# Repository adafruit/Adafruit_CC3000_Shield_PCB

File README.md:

# Adafruit CC3000 Shield PCB
&nbsp; <br />
Click to view in the Adafruit Shop:
- [Adafruit CC3000 WiFi Shield with uFL Connector for Ext Antenna (DISCONTINUED)](https://www.adafruit.com/product/1534)
- [Adafruit HUZZAH CC3000 WiFi Shield with Onboard Antenna (DISCONTINUED)](https://www.adafruit.com/product/1491)

The CC3000 hits that sweet spot of usability, price and capability. It uses SPI for communication (not UART!) so you can push data as fast as you want or as slow as you want. It has a proper interrupt system with IRQ pin so you can have asynchronous connections. It supports 802.11b/g, open/WEP/WPA/WPA2 security, TKIP & AES. A built in TCP/IP stack with a "BSD socket" interface. TCP and UDP in both client and server mode, up to 4 concurrent sockets. It does not support "AP" mode, it can connect to an access point but it cannot be an access point.

**Please note that the CC3000 module is discontinued and we suggest the [Adafruit Airlift products](https://www.adafruit.com/?q=airlift) as a replacement** - it has SSL support, soft-AP capability, and is more reliable.

PCB files for Adafruit CC3000 Shields. The format is EagleCAD schematic and board layout

For more details, check out the product page at

-----> http://www.adafruit.com/products/1534
-----> http://www.adafruit.com/products/1491

### License

Adafruit invests time and resources providing this open source design, please support Adafruit and open-source hardware by [purchasing products from Adafruit](https://www.adafruit.com)!

All text above must be included in any redistribution

Designed by Limor Fried/Ladyada for Adafruit Industries.
Creative Commons Attribution/Share-Alike, all text above must be included in any redistribution. 
See license.txt for additional information.

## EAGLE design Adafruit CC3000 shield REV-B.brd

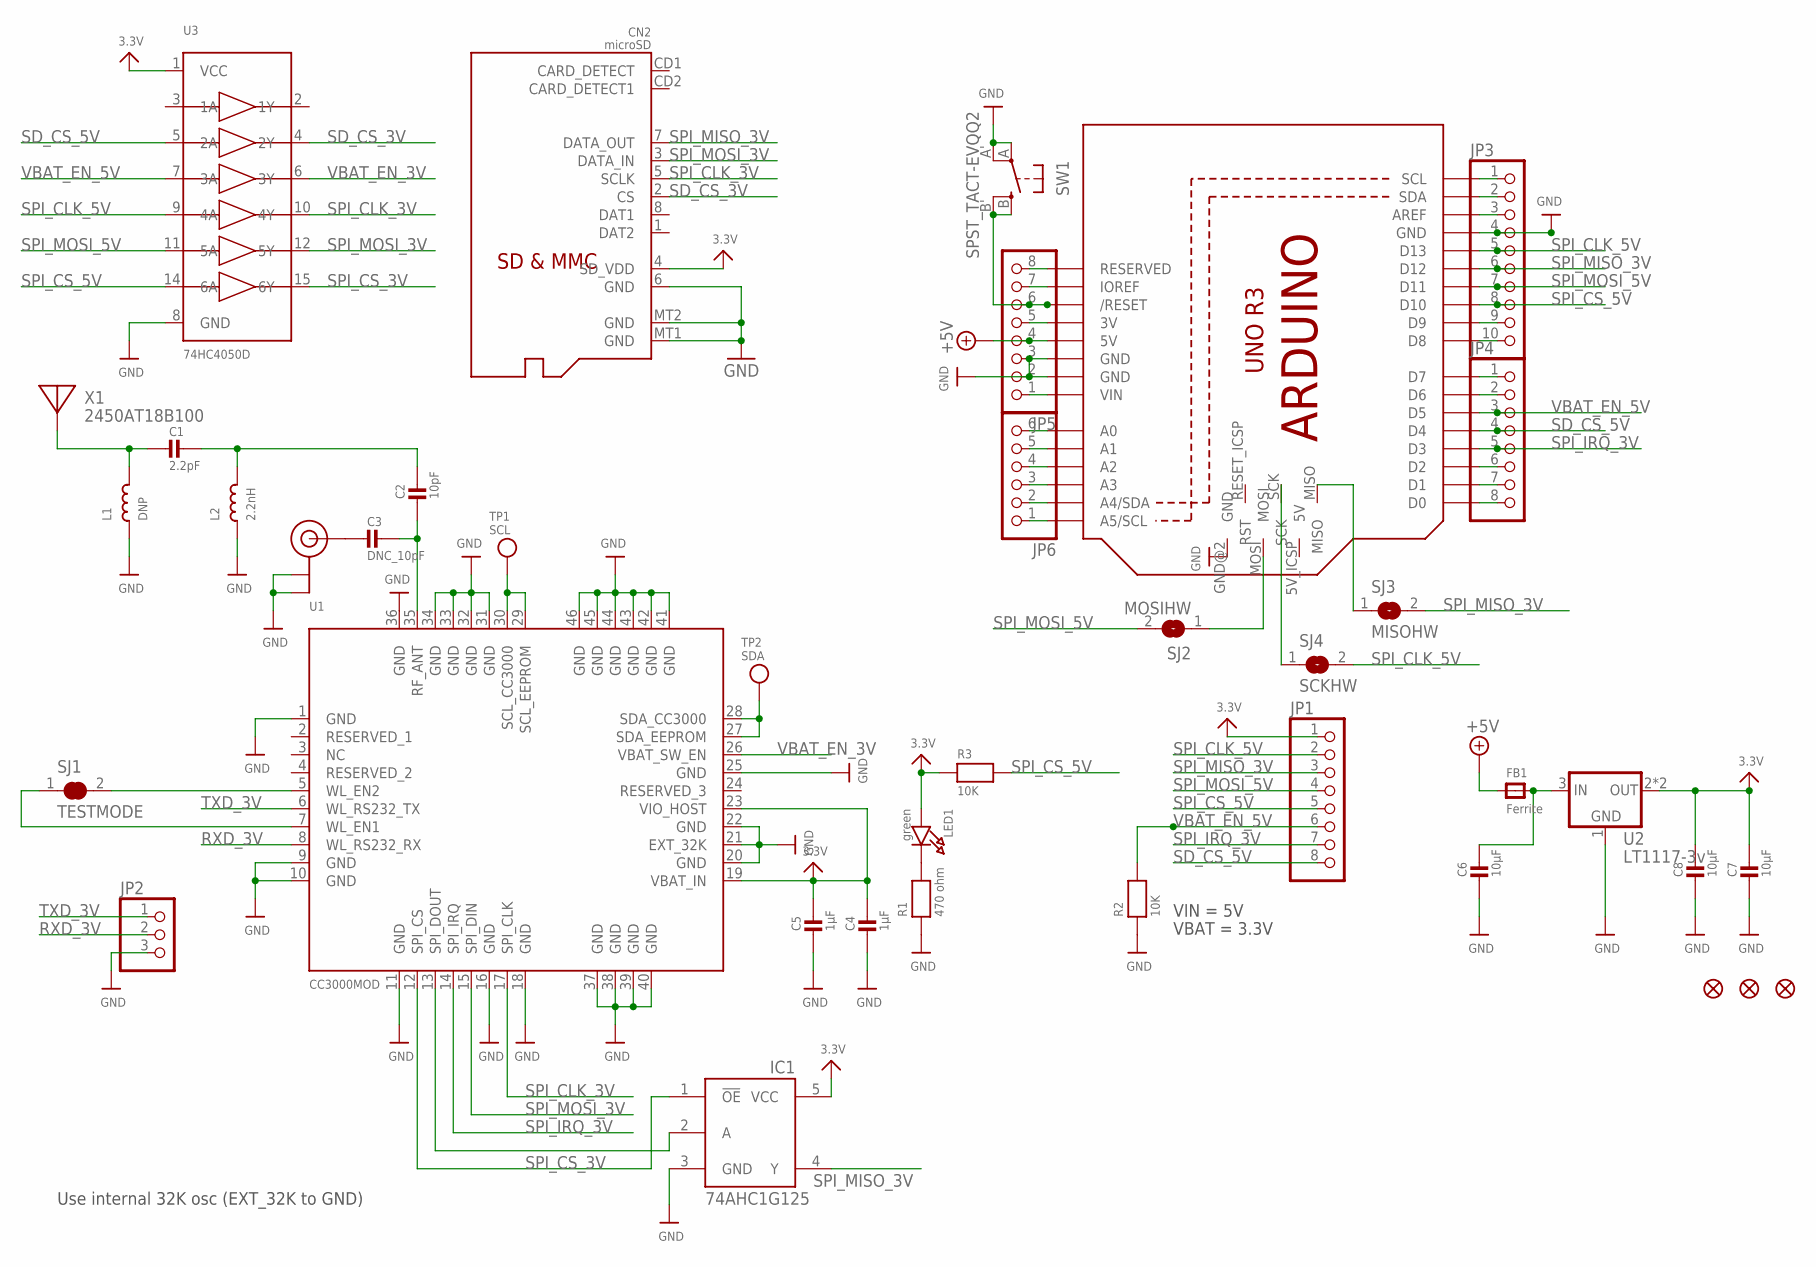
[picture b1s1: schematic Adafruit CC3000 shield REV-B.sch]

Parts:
C1: 2.2pF; _0402
C2: 10pF; _0402
C3: DNC_10pF; _0402
C4, C5: 1µF; _0805MP
C6, C7, C8: 10µF; _0805MP
CN2: microSD; MICROSD
FB1: Ferrite; _0805MP
FID1, FID2, FID3: FIDUCIAL""; FIDUCIAL_1MM
IC1: 74AHC1G125; SOT23-5L
JP1: PINHD-1X8BIG; 1X08-BIG
JP2: HEADER-1X3ROUND; 1X03_ROUND
JP3: HEADER-1X1070MIL; 1X10_ROUND70
JP4, JP5: PINHD-1X8CLEANBIG; 1X08-CLEANBIG
JP6: PINHD-1X6CB; 1X06-CLEANBIG
L1: DNP; _0402
L2: 2.2nH; _0402
LED1: green; CHIPLED_0805_NOOUTLINE
R1: 470 ohm; _0805MP
R2, R3: 10K; _0805MP
SJ1: TESTMODE; SOLDERJUMPER_CLOSEDWIRE
SJ2: MOSIHW; SOLDERJUMPER_ARROW_NOPASTE
SJ3: MISOHW; SOLDERJUMPER_ARROW_NOPASTE
SJ4: SCKHW; SOLDERJUMPER_ARROW_NOPASTE
SW1: SPST_TACT-EVQQ2; EVQ-Q2
TP1: SCL; TESTPOINT_PAD_1MM
TP2: SDA; TESTPOINT_PAD_1MM
U1: CC3000MOD
U2: LT1117-3v; SOT223-R
U3: 74HC4050D; SOIC16
U$35: U.FL
U$36: ARDUINO_R3_ICSP; ARDUINOR3_ICSP
X1: 2450AT18B100; ANT_2500AT44M0400

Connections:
3.3V: C4.1, C5.1, C7.1, C8.1, CN2.4 (SD_VDD), IC1.5 (VCC), JP1.1, LED1.A, R3.1, U1.19 (VBAT_IN), U1.23 (VIO_HOST), U2.2 (OUT), U2.4 (OUT), U3.1 (VCC)
+5V: FB1.1, JP5.4, U$36.5V
GND: C4.2, C5.2, C6.2, C7.2, C8.2, CN2.6 (GND), CN2.MT1 (GND), CN2.MT2 (GND), IC1.3 (GND), JP2.3, JP3.4, JP5.2, JP5.3, L1.1, L2.1, R1.1, R2.1, SW1.A, SW1.A' (P1), U1.1 (GND), U1.9 (GND), U1.10 (GND), U1.11 (GND), U1.16 (GND), U1.18 (GND), U1.20 (GND), U1.21 (EXT_32K), U1.22 (GND), U1.25 (GND), U1.31 (GND), U1.32 (GND), U1.33 (GND), U1.34 (GND), U1.36 (GND), U1.37 (GND), U1.38 (GND), U1.39 (GND), U1.40 (GND), U1.41 (GND), U1.42 (GND), U1.43 (GND), U1.44 (GND), U1.45 (GND), U1.46 (GND), U2.1 (GND), U3.8 (GND), U$35.P$1 (GND), U$35.P$2 (GND), U$36.GND, U$36.GND@1 (GND), U$36.GND@2 (GND), U$36.GND@3 (GND)
unnamed: C1.2, L1.2, X1.FEED
unnamed: C1.1, C2.1, L2.2
unnamed: C3.2, U$35.P$3 (SIGNAL)
unnamed: C2.2, C3.1, U1.35 (RF_ANT)
unnamed: SJ1.2, U1.5 (WL_EN2)
unnamed: SJ1.1, U1.7 (WL_EN1)
unnamed: JP3.1, U$36.SCL
unnamed: JP3.2, U$36.SDA
unnamed: C6.1, FB1.2, U2.3 (IN)
unnamed: JP3.3, U$36.AREF
unnamed: JP5.6, SW1.B (S), SW1.B' (S1), U$36.RESET (/RESET)
unnamed: IC1.2 (A), U1.13 (SPI_DOUT)
unnamed: JP3.9, U$36.D9
unnamed: JP3.10, U$36.D8
unnamed: JP4.1, U$36.D7
unnamed: JP4.2, U$36.D6
unnamed: JP4.6, U$36.D2
unnamed: JP4.7, U$36.D1
unnamed: JP4.8, U$36.D0
unnamed: JP5.1, U$36.VIN
unnamed: JP5.5, U$36.3V
unnamed: JP5.7, U$36.IOREF
unnamed: JP5.8, U$36.RESERVED
unnamed: JP6.1, U$36.A5 (A5/SCL)
unnamed: JP6.2, U$36.A4 (A4/SDA)
unnamed: JP6.3, U$36.A3
unnamed: JP6.4, U$36.A2
unnamed: JP6.5, U$36.A1
unnamed: JP6.6, U$36.A0
unnamed: LED1.C, R1.2
unnamed: SJ2.1, U$36.MOSI
unnamed: SJ4.1, U$36.SCK
unnamed: SJ3.1, U$36.MISO
RXD_3V: JP2.2, U1.8 (WL_RS232_RX)
SCL_3V: TP1.P$1, U1.29 (SCL_EEPROM), U1.30 (SCL_CC3000)
SDA_3V: TP2.P$1, U1.27 (SDA_EEPROM), U1.28 (SDA_CC3000)
SD_CS_3V: CN2.2 (CS), U3.4 (2Y)
SD_CS_5V: JP1.8, JP4.4, U3.5 (2A), U$36.D4
SPI_CLK_3V: CN2.5 (SCLK), U1.17 (SPI_CLK), U3.10 (4Y)
SPI_CLK_5V: JP1.2, JP3.5, SJ4.2, U3.9 (4A), U$36.D13
SPI_CS_3V: IC1.1 (!OE), U1.12 (SPI_CS), U3.15 (6Y)
SPI_CS_5V: JP1.5, JP3.8, R3.2, U3.14 (6A), U$36.D10
SPI_IRQ_3V: JP1.7, JP4.5, U1.14 (SPI_IRQ), U$36.D3
SPI_MISO_3V: CN2.7 (DATA_OUT), IC1.4 (Y), JP1.3, JP3.6, SJ3.2, U$36.D12
SPI_MOSI_3V: CN2.3 (DATA_IN), U1.15 (SPI_DIN), U3.12 (5Y)
SPI_MOSI_5V: JP1.4, JP3.7, SJ2.2, U3.11 (5A), U$36.D11
TXD_3V: JP2.1, U1.6 (WL_RS232_TX)
VBAT_EN_3V: U1.26 (VBAT_SW_EN), U3.6 (3Y)
VBAT_EN_5V: JP1.6, JP4.3, R2.2, U3.7 (3A), U$36.D5

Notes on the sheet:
Use internal 32K osc (EXT_32K to GND)
VIN = 5V
VBAT = 3.3V

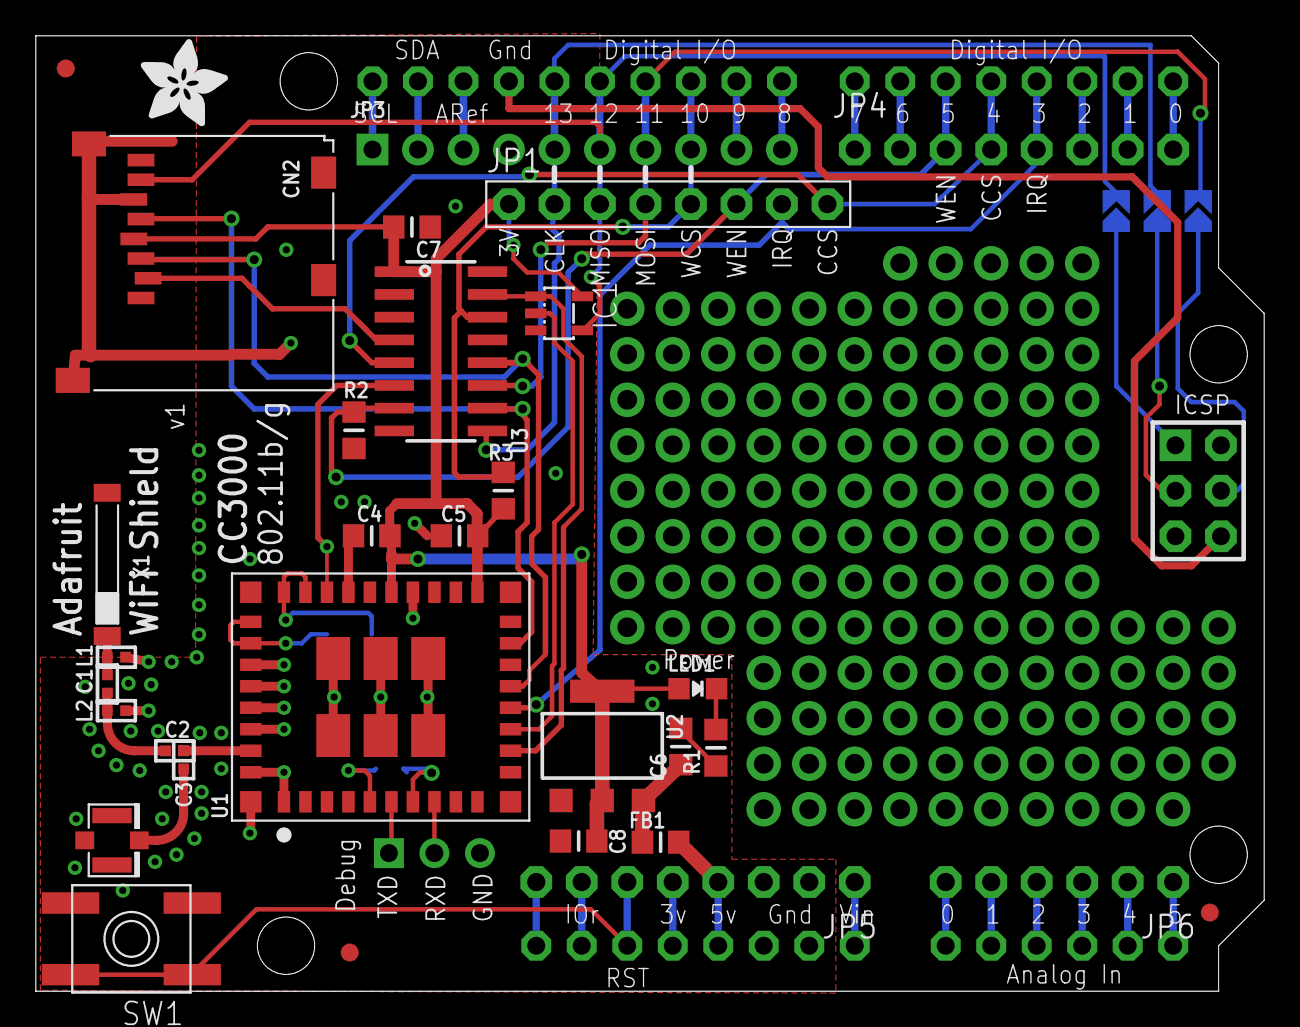
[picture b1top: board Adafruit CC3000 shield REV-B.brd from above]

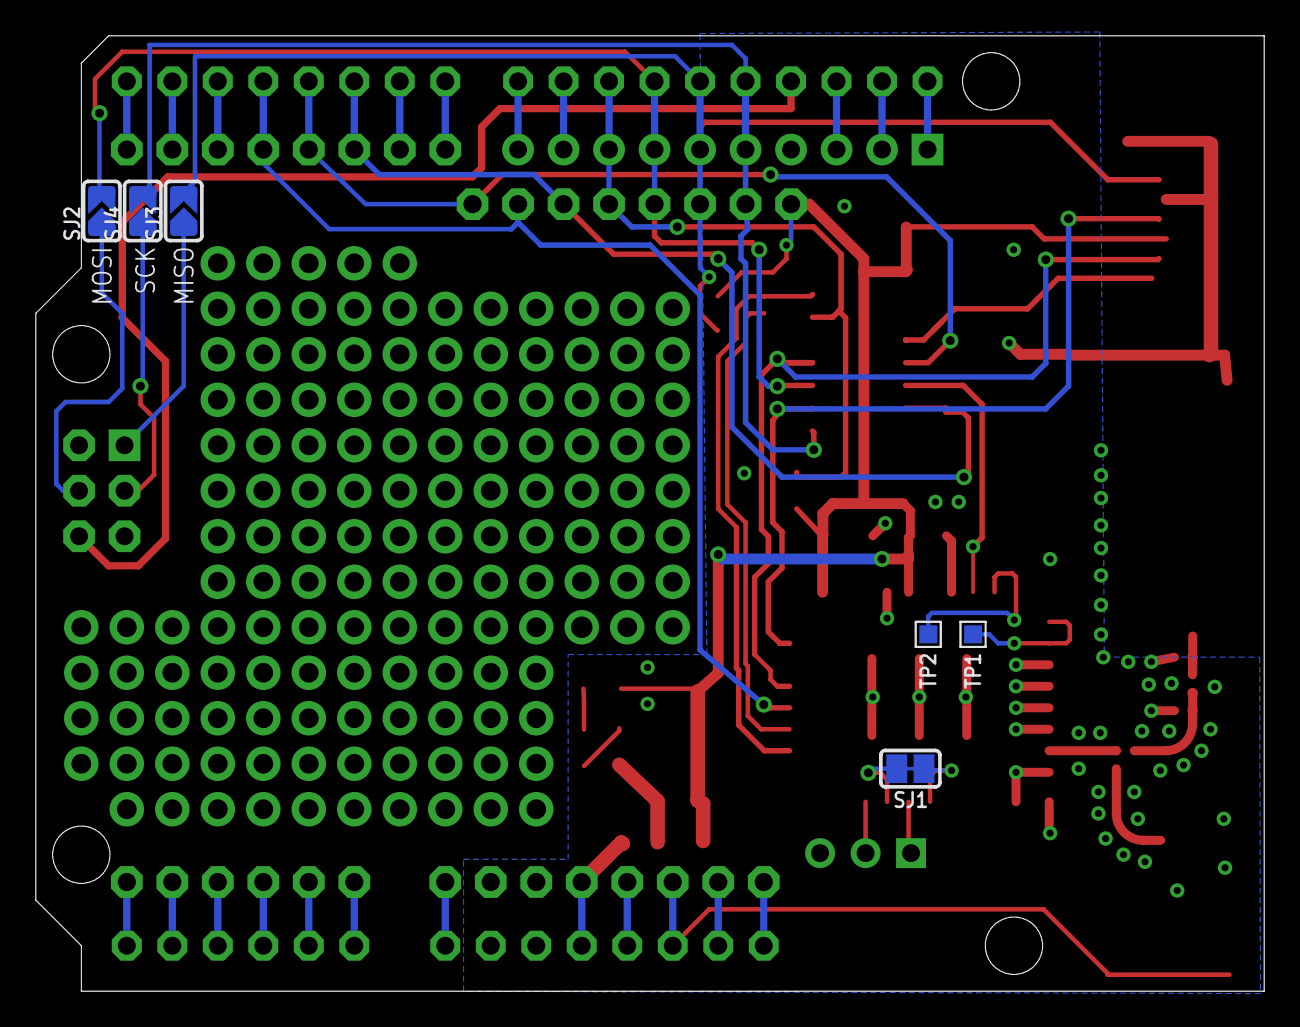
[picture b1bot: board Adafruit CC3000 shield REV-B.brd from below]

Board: 2 copper layers, 68.6 x 53.3 mm, 40 parts (6 on the bottom side), 52 nets.

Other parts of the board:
U$8: ADAFRUIT_5MM

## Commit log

2014-09-02 init

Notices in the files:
parts and their libraries:
microbuilder: This work is placed in the public domain, and may be freely used for commercial and non-commercial work with the following conditions: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
